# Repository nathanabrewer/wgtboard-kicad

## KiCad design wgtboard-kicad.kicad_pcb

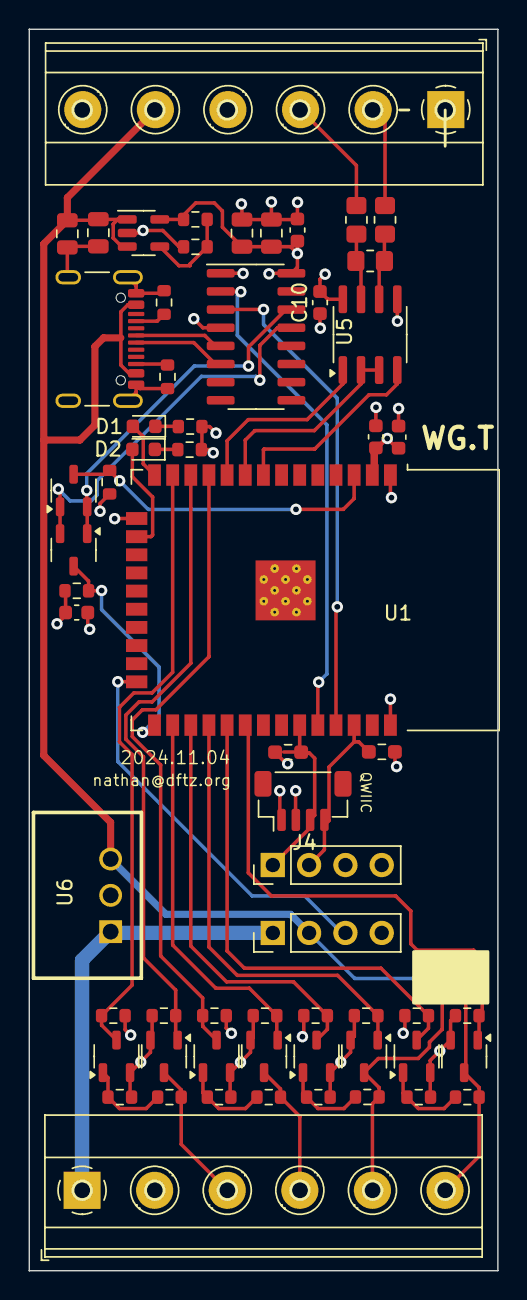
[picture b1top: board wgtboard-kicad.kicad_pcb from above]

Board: 4 copper layers, 32.8 x 86.9 mm, 63 parts (0 on the bottom side), 45 nets.

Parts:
C1, C4, C7, C10: 0.1uF 16v; C_0603_1608Metric
C2, C5, C6: 47uF 16V; C_0805_2012Metric
C3: 1uF 16V; C_0805_2012Metric
C8: 22uF 16v; C_0603_1608Metric
D1, D2: LED; LED_0603_1608Metric
J1, J3: Conn_01x04_Socket; PinHeader_1x04_P2.54mm_Vertical
J2, J7: Screw_Terminal_01x06; TerminalBlock_Phoenix_MKDS-1,5-6-5.08_1x06_P5.08mm_Horizont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
J4: Conn_01x04_Socket; JST_SH_BM04B-SRSS-TB_1x04-1MP_P1.00mm_Vertical
P1: C2927039; USB_C_Receptacle_GCT_USB4105-xx-A_16P_TopMnt_Horizontal
Q1, Q2, Q10, Q11, Q12, Q13, Q14, Q15, Q16, Q17: BSS138; SOT-23-3
R1, R9: 10; R_0805_2012Metric_Pad1.20x1.40mm_HandSolder
R2: 56k; R_0603_1608Metric
R3: 33k; R_0603_1608Metric
R4, R17: 5.1k; R_0603_1608Metric
R5, R6, R19, R20: 10k; R_0603_1608Metric
R7: 270; R_0805_2012Metric_Pad1.20x1.40mm_HandSolder
R10, R16, R28, R30, R32, R34, R36, R38: 1k; R_0603_1608Metric
R11, R26, R29, R31, R33, R35, R37, R39: 20k; R_0603_1608Metric
R12, R13: 10k; R_0603_1608Metric_Pad0.98x0.95mm_HandSolder
R14, R15: 330; R_0603_1608Metric
U1: ESP32-WROOM-32
U2: CH340C; SOIC-16_3.9x9.9mm_P1.27mm
U3: C9056; SOT-23-5
U5: MAX3485; SOIC-8_3.9x4.9mm_P1.27mm
U6: K7805M-1000R3_C5369649; PWRM-TH_DEXU_K780XM-1000R3

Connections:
+3.3V: C1.2, C4.2, C5.2, C6.2, C7.2, C8.2, C10.2, J2.4, J3.3, J4.2, R2.1, R5.2, R6.2, R12.2, R13.2, R16.2, R30.2, R34.2, R38.2, U1.2 (VDD), U2.4 (V3), U2.16 (VCC), U3.5 (OUT), U5.8 (VCC)
/5V: C2.2, C3.2, J1.2, J2.5, P1.A4 (VBUS), P1.A9 (VBUS), P1.B4 (VBUS), P1.B9 (VBUS), R19.2, R20.2, U3.1 (IN), U3.3 (EN), U6.3 (VO)
/A: J2.2, R1.2
/B: J2.3, R9.2
/Boot: Q2.3 (D), R6.1, U1.25 (IO0)
/EN: Q1.3 (D), R5.1, U1.3 (EN)
/IO2: J1.3, U1.24 (IO2)
/MCU_RX: U1.34 (RXD0/IO3), U2.2 (TXD)
/MCU_TX: U1.35 (TXD0/IO1), U2.3 (RXD)
/RS485_HL: U1.9 (IO33), U5.2 (~RE), U5.3 (DE)
/RS485_RX: U1.10 (IO25), U5.1 (RO)
/RS485_TX: U1.8 (IO32), U5.4 (DI)
/SCL: J3.2, J4.4, R12.1, U1.36 (IO22)
/SDA: J3.1, J4.3, R13.1, U1.33 (IO21)
/VIN: J1.1, J7.1, U6.1 (VIN)
/WG_BUZZ: J7.6, Q17.3 (D), R20.1, R36.1
/WG_BUZZ_IN_3V3: Q16.3 (D), R38.1, U1.29 (IO5)
/WG_D0: J7.3, Q11.3 (D), R10.1
/WG_D0_IN_3V3: Q10.3 (D), R16.1, U1.13 (IO14)
/WG_D1: J7.4, Q13.3 (D), R28.1
/WG_D1_IN_3V3: Q12.3 (D), R30.1, U1.11 (IO26)
/WG_LED1: J7.5, Q15.3 (D), R19.1, R32.1
/WG_LED_IN_3V3: Q14.3 (D), R34.1, U1.27 (IO16)
/WG_PULL_BUZZ: Q17.1 (G), R39.2, U1.30 (IO18)
/WG_PULL_D0: Q11.1 (G), R26.2, U1.12 (IO27)
/WG_PULL_D1: Q13.1 (G), R31.2, U1.26 (IO4)
/WG_PULL_LED: Q15.1 (G), R35.2, U1.28 (IO17)
GND: C1.1, C2.1, C3.1, C4.1, C5.1, C6.1, C7.1, C8.1, C10.1, J1.4, J2.1, J2.6, J3.4, J4.1, J7.2, P1.A1 (GND), P1.A12 (GND), P1.B1 (GND), P1.B12 (GND), P1.S1 (SHIELD), Q10.2 (S), Q11.2 (S), Q12.2 (S), Q13.2 (S), Q14.2 (S), Q15.2 (S), Q16.2 (S), Q17.2 (S), R3.2, R4.2, R11.1, R14.2, R15.2, R17.2, R26.1, R29.1, R31.1, R33.1, R35.1, R37.1, R39.1, U1.1 (GND), U1.15 (GND), U1.38 (GND), U1.39 (GND), U2.1 (GND), U3.2 (GND), U5.5 (GND), U6.2 (GND)
unnamed: D1.2 (A), U1.14 (IO12)
unnamed: D1.1 (K), R14.1
unnamed: D2.2 (A), U1.16 (IO13)
unnamed: D2.1 (K), R15.1
unnamed: P1.A5 (CC), R17.1
unnamed: P1.A6 (D+), U2.5 (UD+)
unnamed: P1.A7 (D-), U2.6 (UD-)
unnamed: P1.B5 (VCONN), R4.1
unnamed: Q1.1 (G), Q2.2 (S), U2.13 (~DTR)
unnamed: Q1.2 (S), Q2.1 (G), U2.14 (~RTS)
unnamed: Q10.1 (G), R10.2, R11.2
unnamed: Q12.1 (G), R28.2, R29.2
unnamed: Q14.1 (G), R32.2, R33.2
unnamed: Q16.1 (G), R36.2, R37.2
unnamed: R2.2, R3.1, U3.4 (ADJ)
unnamed: R1.1, R7.1, U5.6 (A)
unnamed: R7.2, R9.1, U5.7 (B)
